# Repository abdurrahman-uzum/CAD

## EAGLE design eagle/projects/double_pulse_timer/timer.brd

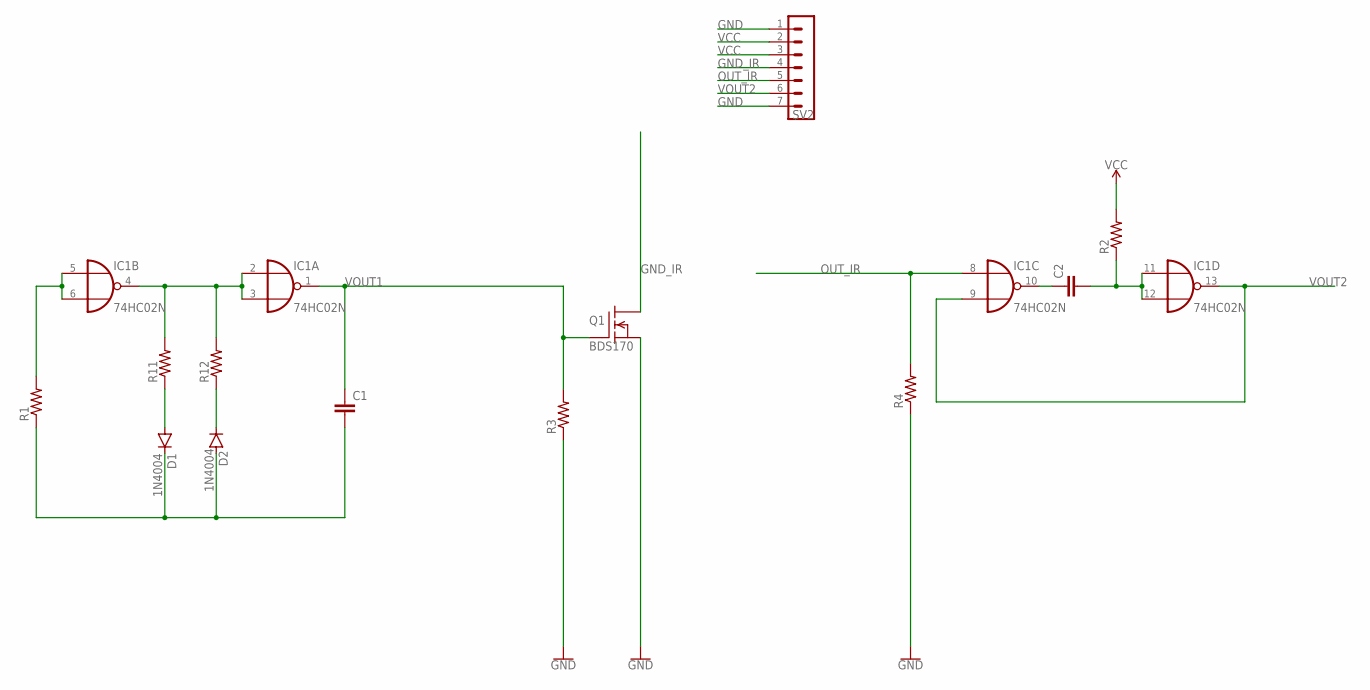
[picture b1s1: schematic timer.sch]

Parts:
C1: C-EU025-024X044; C025-024X044
C2: C-EU050-025X075; C050-025X075
D1, D2: 1N4004; DO41-10
IC1: 74HC02N; DIL14
Q1: VN10KM; TO92-
R1, R2, R3, R4, R11, R12: R-US_0207/10; 0207/10
SV2: MA07-1

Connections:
GND: IC1.7 (GND), Q1.3 (S), R3.1, R4.1, SV2.1, SV2.7
GND_IR: Q1.1 (D), SV2.4
unnamed: IC1.2 (I0), IC1.3 (I1), IC1.4 (O), R11.2, R12.2
unnamed: IC1.5 (I0), IC1.6 (I1), R1.2
unnamed: D1.A, R11.1
unnamed: D2.C, R12.1
unnamed: C1.2, D1.C, D2.A, R1.1
unnamed: C2.2, IC1.11 (I0), IC1.12 (I1), R2.1
unnamed: C2.1, IC1.10 (O)
OUT_IR: IC1.8 (I0), R4.2, SV2.5
VCC: IC1.14 (VCC), R2.2, SV2.2, SV2.3
VOUT1: C1.1, IC1.1 (O), Q1.2 (G), R3.2
VOUT2: IC1.9 (I1), IC1.13 (O), SV2.6

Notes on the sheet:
BDS170

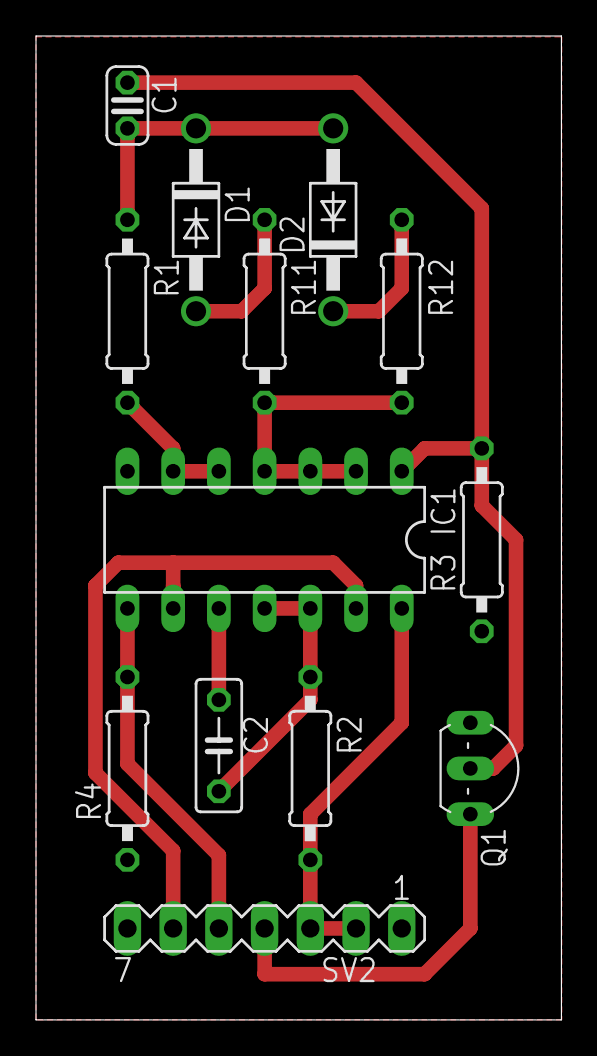
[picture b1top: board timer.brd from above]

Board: 2 copper layers, 29.2 x 54.7 mm, 13 parts (0 on the bottom side), 13 nets.

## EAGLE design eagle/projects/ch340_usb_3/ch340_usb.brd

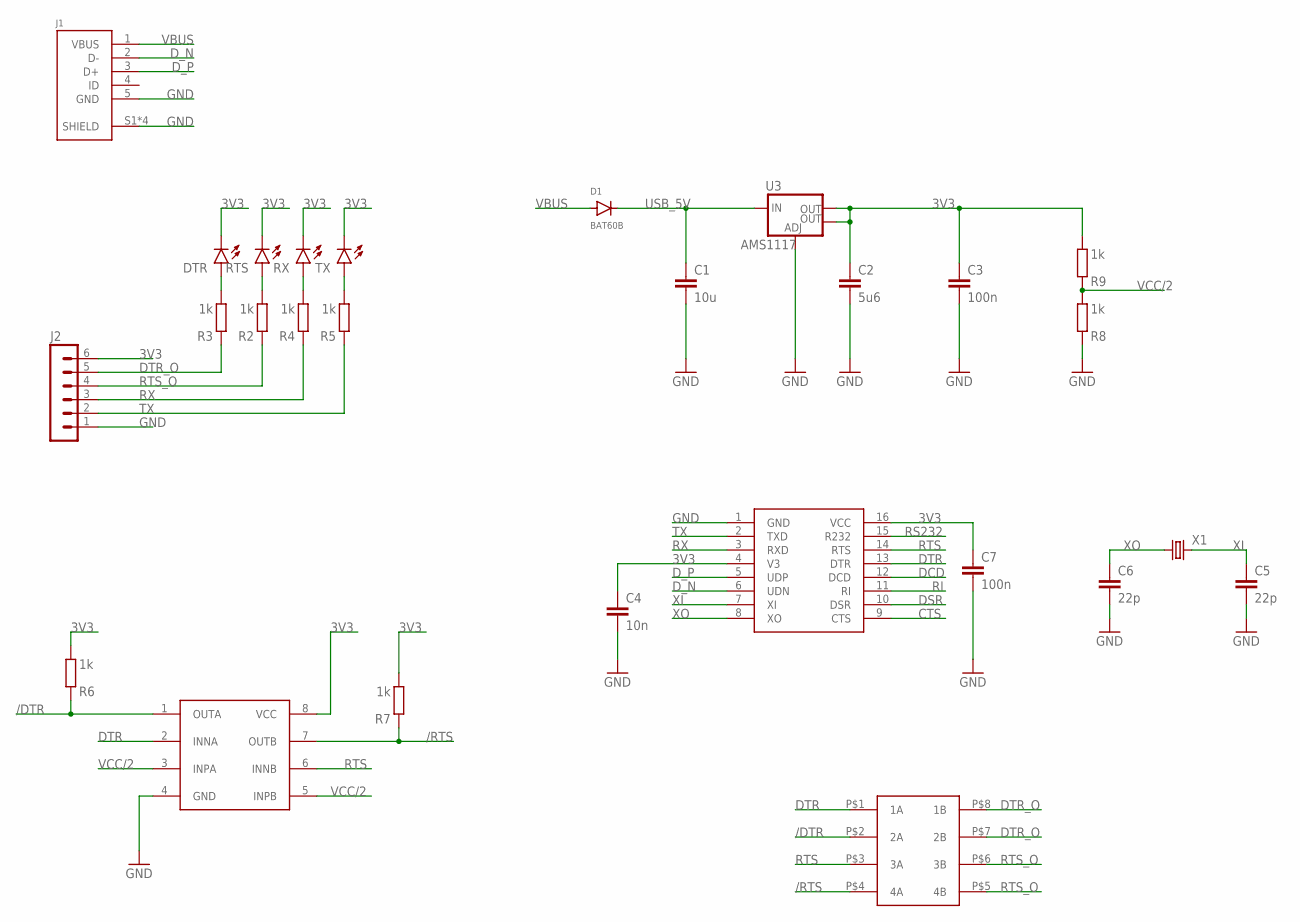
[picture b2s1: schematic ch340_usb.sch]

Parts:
C1: 10u; C0805K
C2: 5u6; C0805K
C3, C7: 100n; C0805K
C4: 10n; C0805K
C5, C6: 22p; C0805K
D1: BAT60B; SOD123
DTR: PWR; CHIPLED_0805
J1: 1734035-4
J2: MA06-1
R2, R3, R4, R5, R6, R7, R8, R9: 1k; R0805
RTS: PWR; CHIPLED_0805
RX: PWR; CHIPLED_0805
TX: PWR; CHIPLED_0805
U1: HX711; SOP16
U2: LM393; SOIC127P600X144-8
U3: AMS1117; SOT223
U$1: DIPSW4; 4_SMT_2.54
X1: CSM-7X-DU

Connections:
3V3: C2.1, C3.1, C4.1, C7.1, DTR.C, J2.6, R6.1, R7.1, R9.1, RTS.C, RX.C, TX.C, U1.4 (V3), U1.16 (VCC), U2.8 (VCC), U3.2 (OUT), U3.4 (OUT)
/DTR: R6.2, U2.1 (OUTA), U$1.P$2 (2A)
/RTS: R7.2, U2.7 (OUTB), U$1.P$4 (4A)
CTS: U1.9 (CTS)
DCD: U1.12 (DCD)
DSR: U1.10 (DSR)
DTR: U1.13 (DTR), U2.2 (INNA), U$1.P$1 (1A)
DTR_O: J2.5, R3.2, U$1.P$7 (2B), U$1.P$8 (1B)
D_N: J1.2 (D-), U1.6 (UDN)
D_P: J1.3 (D+), U1.5 (UDP)
GND: C1.2, C2.2, C3.2, C4.2, C5.2, C6.2, C7.2, J1.5 (GND), J1.S1 (SHIELD), J1.S2 (SHIELD), J1.S3 (SHIELD), J1.S4 (SHIELD), J2.1, R8.2, U1.1 (GND), U2.4 (GND), U3.1 (ADJ)
unnamed: DTR.A, R3.1
unnamed: R2.1, RTS.A
unnamed: R4.1, RX.A
unnamed: R5.1, TX.A
RI: U1.11 (RI)
RS232: U1.15 (R232)
RTS: U1.14 (RTS), U2.6 (INNB), U$1.P$3 (3A)
RTS_O: J2.4, R2.2, U$1.P$5 (4B), U$1.P$6 (3B)
RX: J2.3, R4.2, U1.3 (RXD)
TX: J2.2, R5.2, U1.2 (TXD)
USB_5V: C1.1, D1.C, U3.3 (IN)
VBUS: D1.A, J1.1 (VBUS)
VCC/2: R8.1, R9.2, U2.3 (INPA), U2.5 (INPB)
XI: C5.1, U1.7 (XI), X1.2
XO: C6.1, U1.8 (XO), X1.1

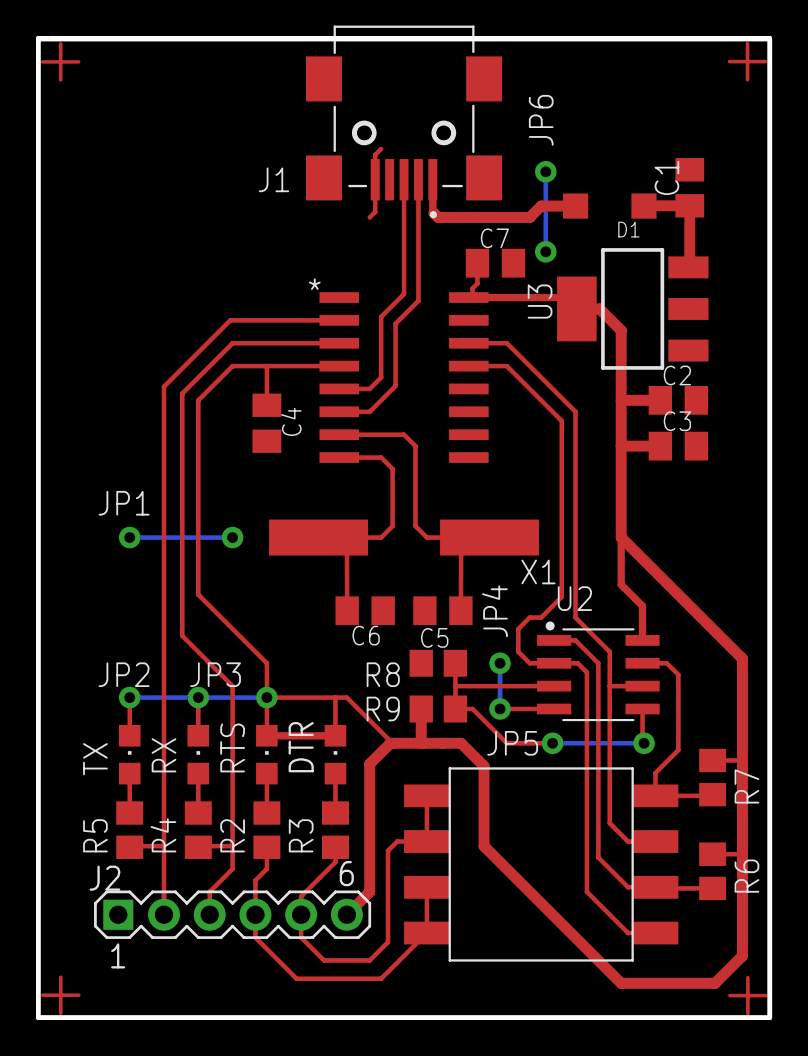
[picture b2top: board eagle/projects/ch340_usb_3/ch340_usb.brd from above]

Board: 2 copper layers, 40.6 x 54.4 mm, 27 parts (0 on the bottom side), 21 nets.

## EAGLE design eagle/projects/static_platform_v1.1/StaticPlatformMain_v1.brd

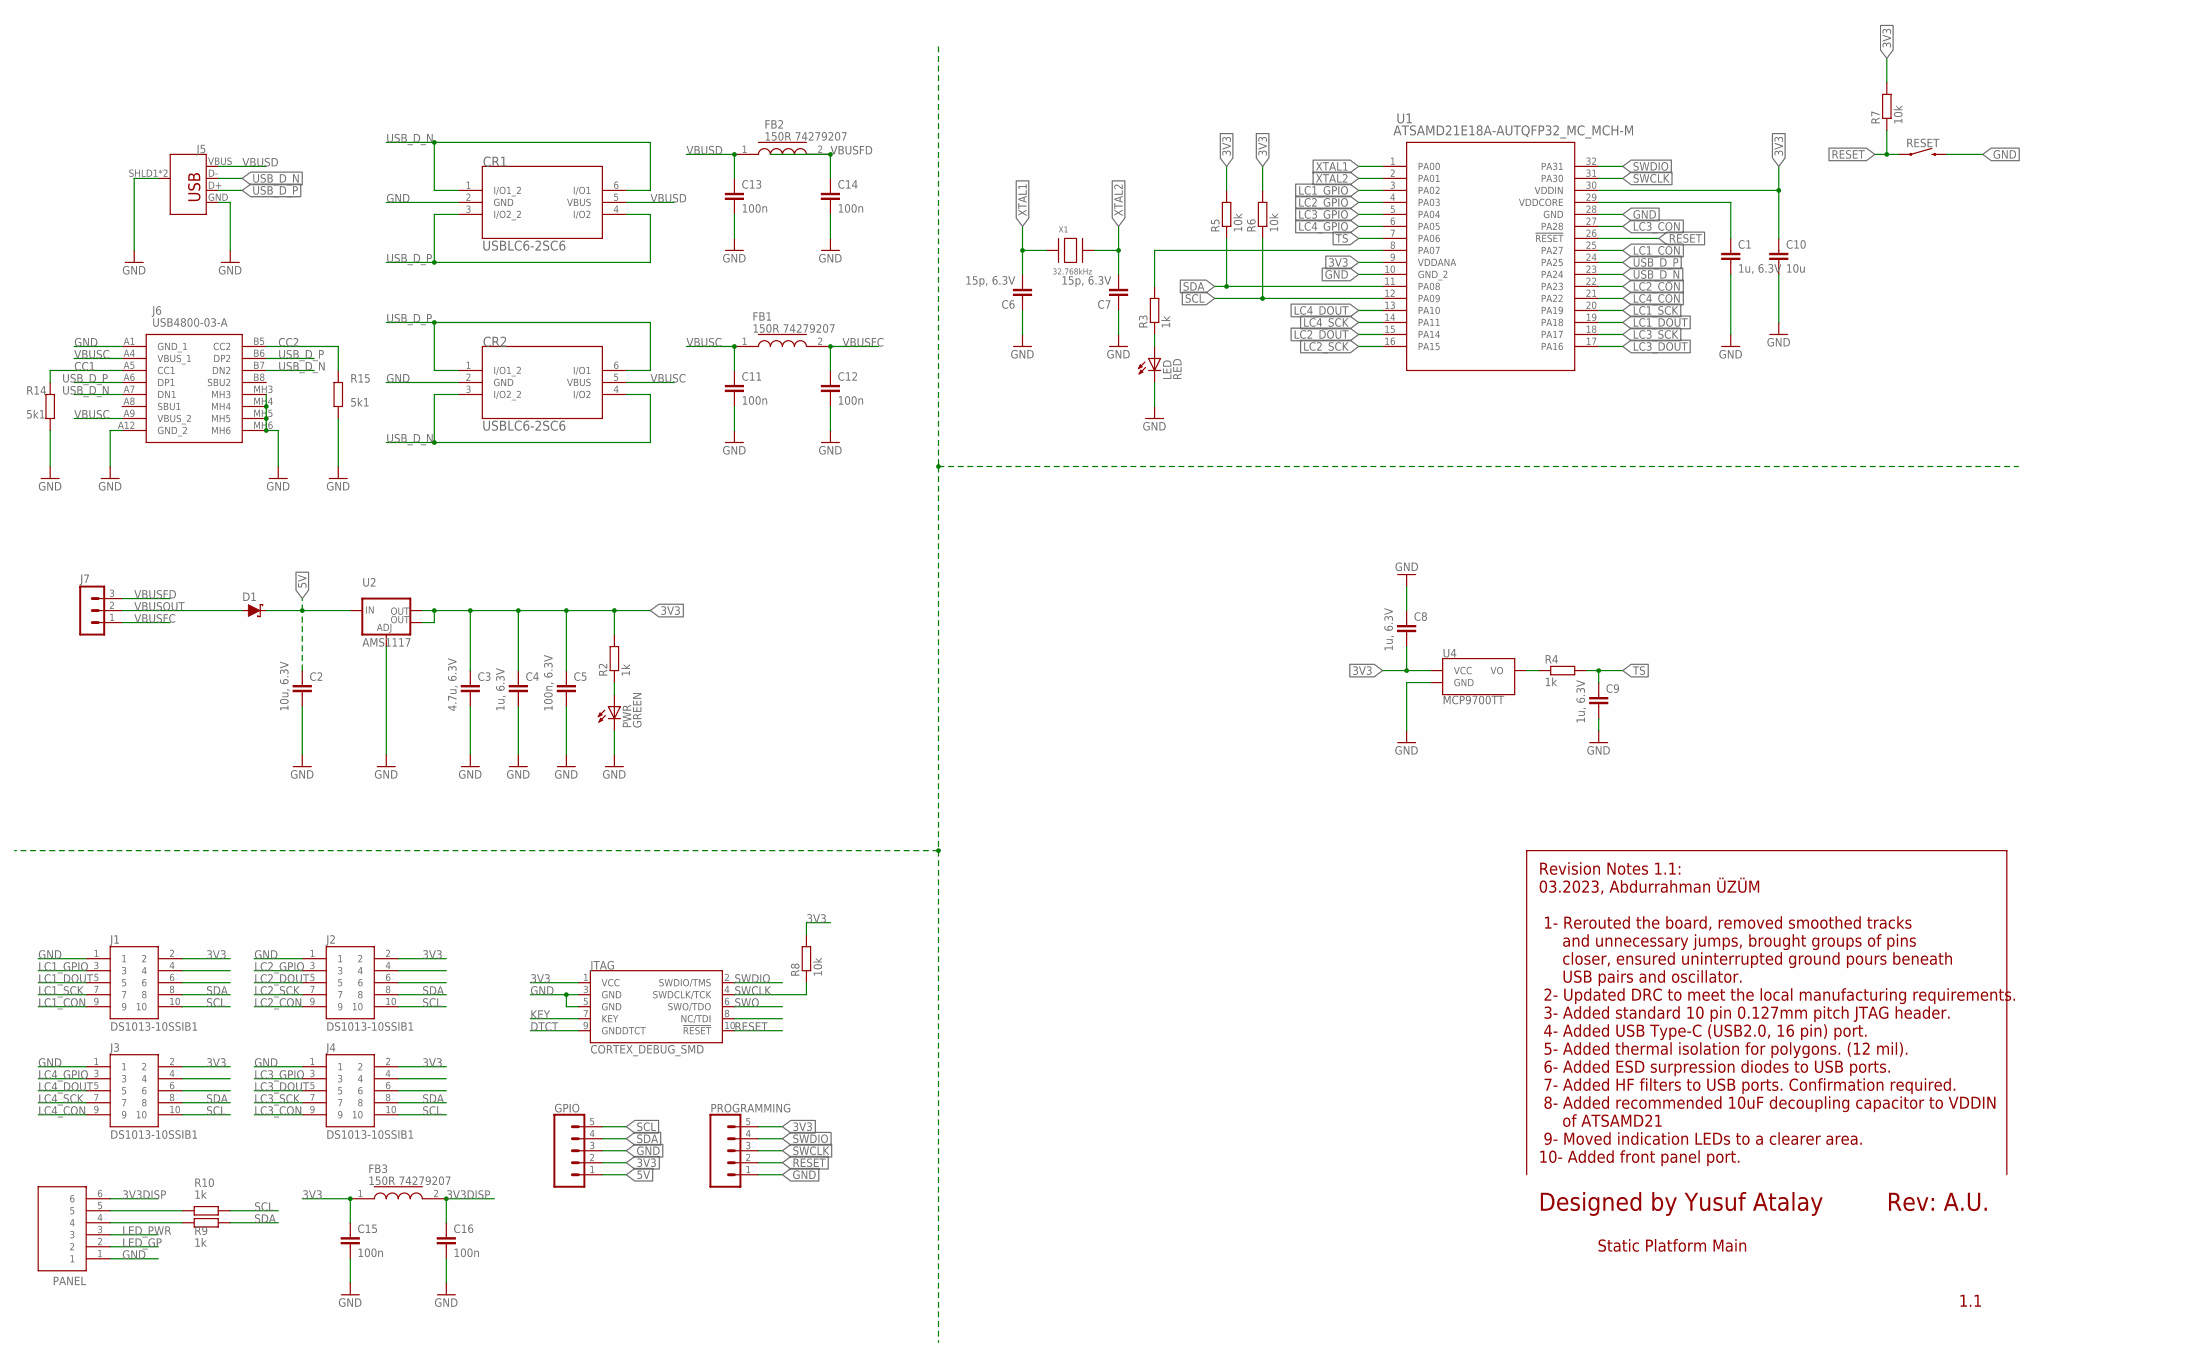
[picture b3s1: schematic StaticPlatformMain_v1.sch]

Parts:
C1, C4, C8, C9: 1u, 6.3V; C0805
C2: 10u, 6.3V; C0805
C3: 4.7u, 6.3V; C0805
C5: 100n, 6.3V; C0805
C6, C7: 15p, 6.3V; C0805
C10: 10u; C0805
C11, C12, C13, C14, C15, C16: 100n; C0805
CR1, CR2: USBLC6-2SC6; SOT23-6L_STM
D1: 3A/10V/280mV; SOD-323
FB1, FB2, FB3: 150R 74279207; CAPC2012X90N
GPIO: CONN_05NO_SILK; 1X05_NO_SILK
J1, J2, J3, J4: DS1013-10SSIB1; CONNFLY_DS1013-10SSIB1
J5: USB_B_PTH; USB-B-PTH
J6: USB4800-03-A; USB480003A
J7: MA03-1
JTAG: CORTEX_DEBUG_SMD; SAMTECH_FTSH-105-01
LED: RED; CHIPLED_0805
PANEL: S3B-XH-A(LF)(SN); JST_S3B-XH-A(LF)(SN)
PROGRAMMING: CONN_05NO_SILK; 1X05_NO_SILK
PWR: GREEN; CHIPLED_0805
R2, R3, R4, R9, R10: 1k; R0805
R5, R6, R7, R8: 10k; R0805
R14, R15: 5k1; R0805
RESET: MOMENTARY-SWITCH-SPST-SMD-6.0X3.5MM; TACTILE_SWITCH_SMD_6.0X3.5MM
U1: ATSAMD21E18A-AUTQFP32_MC_MCH-M; TQFP32_MC_MCH-M
U2: AMS1117; SOT223
U4: MCP9700TT; SOT23-3
X1: 32.768kHz; XTAL3215

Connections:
3V1: R3.2, U1.8 (PA07)
3V3: C3.1, C4.1, C5.1, C8.2, C10.1, C15.1, FB3.1, GPIO.2, J1.2, J2.2, J3.2, J4.2, JTAG.1 (VCC), PROGRAMMING.5, R2.2, R5.2, R6.2, R7.2, R8.2, U1.9 (VDDANA), U1.30 (VDDIN), U2.2 (OUT), U2.4 (OUT), U4.1 (VCC)
3V3DISP: C16.1, FB3.2, PANEL.6
5V: C2.1, D1.C, GPIO.1, U2.3 (IN)
CC1: J6.A5 (CC1), R14.2
CC2: J6.B5 (CC2), R15.2
DTCT: JTAG.9 (GNDDTCT)
GND: C1.2, C2.2, C3.2, C4.2, C5.2, C6.1, C7.1, C8.1, C9.2, C10.2, C11.2, C12.2, C13.2, C14.2, C15.2, C16.2, CR1.2 (GND), CR2.2 (GND), GPIO.3, J1.1, J2.1, J3.1, J4.1, J5.GND, J5.SHLD1 (SHIELD), J5.SHLD2 (SHIELD), J6.A1 (GND_1), J6.A12 (GND_2), J6.MH3, J6.MH4, J6.MH5, J6.MH6, JTAG.3 (GND), JTAG.5 (GND), LED.C, PANEL.1, PROGRAMMING.1, PWR.C, R14.1, R15.1, RESET.2, U1.10 (GND_2), U1.28 (GND), U2.1 (ADJ), U4.3 (GND)
KEY: JTAG.7 (KEY)
LC1_CON: J1.9, U1.25 (PA27)
LC1_DOUT: J1.5, U1.19 (PA18)
LC1_GPIO: J1.3, U1.3 (PA02)
LC1_SCK: J1.7, U1.20 (PA19)
LC2_CON: J2.9, U1.22 (PA23)
LC2_DOUT: J2.5, U1.15 (PA14)
LC2_GPIO: J2.3, U1.4 (PA03)
LC2_SCK: J2.7, U1.16 (PA15)
LC3_CON: J4.9, U1.27 (PA28)
LC3_DOUT: J4.5, U1.17 (PA16)
LC3_GPIO: J4.3, U1.5 (PA04)
LC3_SCK: J4.7, U1.18 (PA17)
LC4_CON: J3.9, U1.21 (PA22)
LC4_DOUT: J3.5, U1.13 (PA10)
LC4_GPIO: J3.3, U1.6 (PA05)
LC4_SCK: J3.7, U1.14 (PA11)
LED_GP: LED.A, PANEL.2, R3.1
LED_PWR: PANEL.3, PWR.A, R2.1
unnamed: PANEL.5, R10.2
unnamed: PANEL.4, R9.2
unnamed: C1.1, U1.29 (VDDCORE)
unnamed: R4.1, U4.2 (VO)
RESET: JTAG.10 (!RESET), PROGRAMMING.2, R7.1, RESET.1, U1.26 (!RESET)
SCL: GPIO.5, J1.10, J2.10, J3.10, J4.10, R6.1, R10.1, U1.12 (PA09)
SDA: GPIO.4, J1.8, J2.8, J3.8, J4.8, R5.1, R9.1, U1.11 (PA08)
SWCLK: JTAG.4 (SWDCLK/TCK), PROGRAMMING.3, R8.1, U1.31 (PA30)
SWDIO: JTAG.2 (SWDIO/TMS), PROGRAMMING.4, U1.32 (PA31)
SWO: JTAG.6 (SWO/TDO)
TS: C9.1, R4.2, U1.7 (PA06)
USB_D_N: CR1.1 (I/O1_2), CR1.6 (I/O1), CR2.3 (I/O2_2), CR2.4 (I/O2), J5.D-, J6.A7 (DN1), J6.B7 (DN2), U1.23 (PA24)
USB_D_P: CR1.3 (I/O2_2), CR1.4 (I/O2), CR2.1 (I/O1_2), CR2.6 (I/O1), J5.D+, J6.A6 (DP1), J6.B6 (DP2), U1.24 (PA25)
VBUSC: C11.1, CR2.5 (VBUS), FB1.1, J6.A4 (VBUS_1), J6.A9 (VBUS_2)
VBUSD: C13.1, CR1.5 (VBUS), FB2.1, J5.VBUS
VBUSFC: C12.1, FB1.2, J7.1
VBUSFD: C14.1, FB2.2, J7.3
VBUSOUT: D1.A, J7.2
XTAL1: C6.2, U1.1 (PA00), X1.P$1
XTAL2: C7.2, U1.2 (PA01), X1.P$2

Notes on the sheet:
Designed by Yusuf Atalay
Rev: A.U.
Static Platform Main
1.1
Revision Notes 1.1: 03.2023, Abdurrahman ÜZÜM 1- Rerouted the board, removed smoothed tracks and unnecessary jumps, brought groups of pins closer, ensured uninterrupted ground pours beneath USB pairs and oscillator. 2- Updated DRC to meet the local manufacturing requirements. 3- Added standard 10 p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

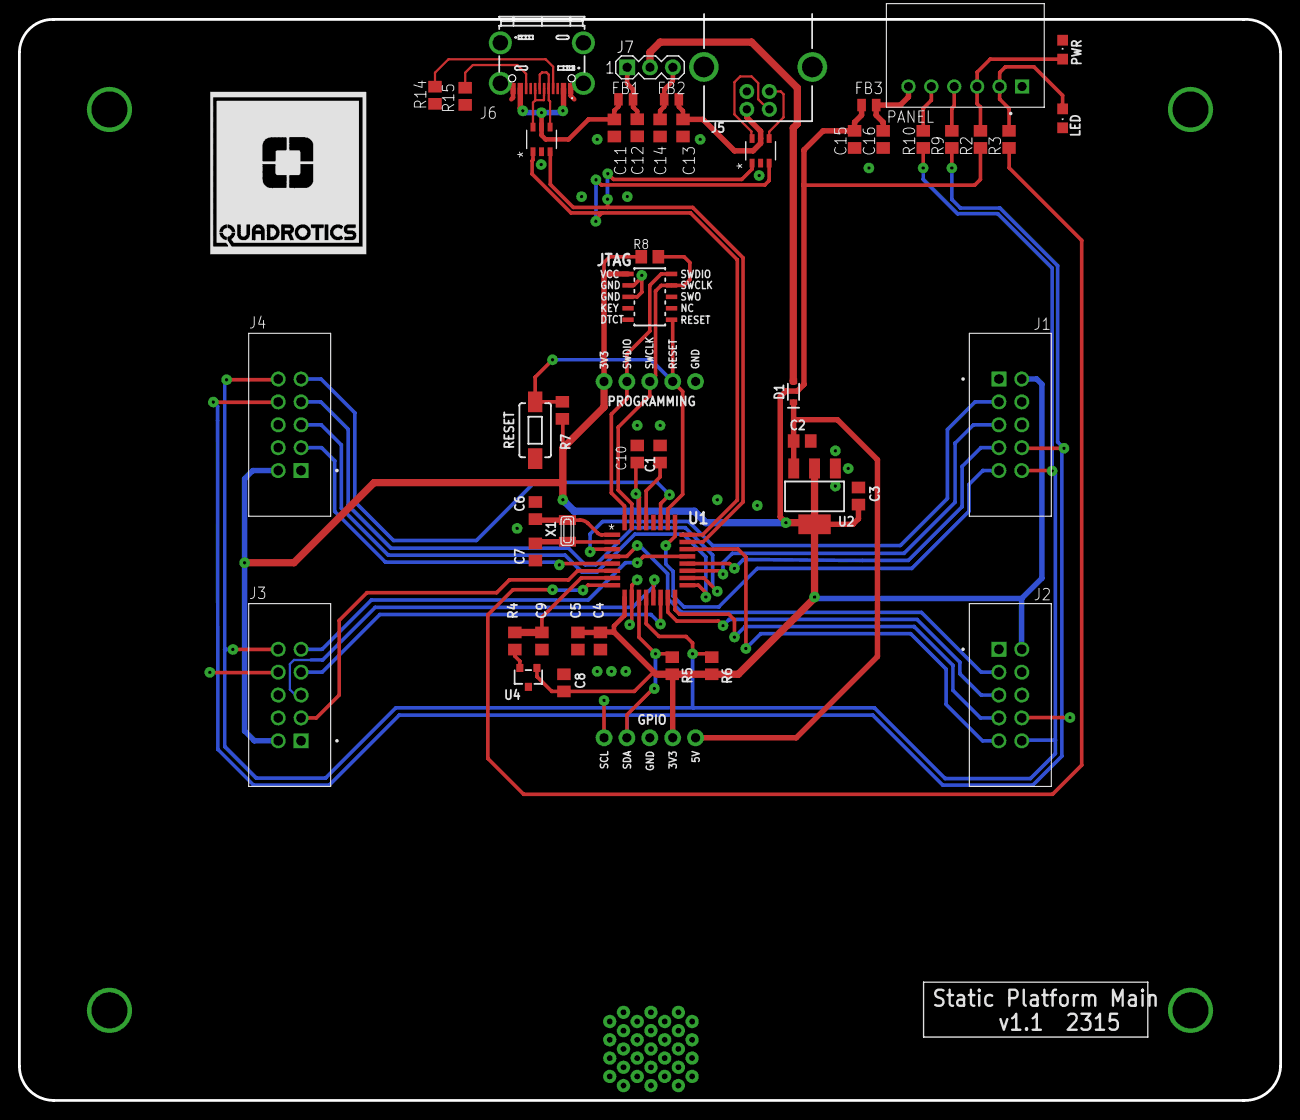
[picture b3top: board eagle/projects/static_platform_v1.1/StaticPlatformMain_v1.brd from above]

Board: 2 copper layers, 140.0 x 120.0 mm, 51 parts (0 on the bottom side), 44 nets.

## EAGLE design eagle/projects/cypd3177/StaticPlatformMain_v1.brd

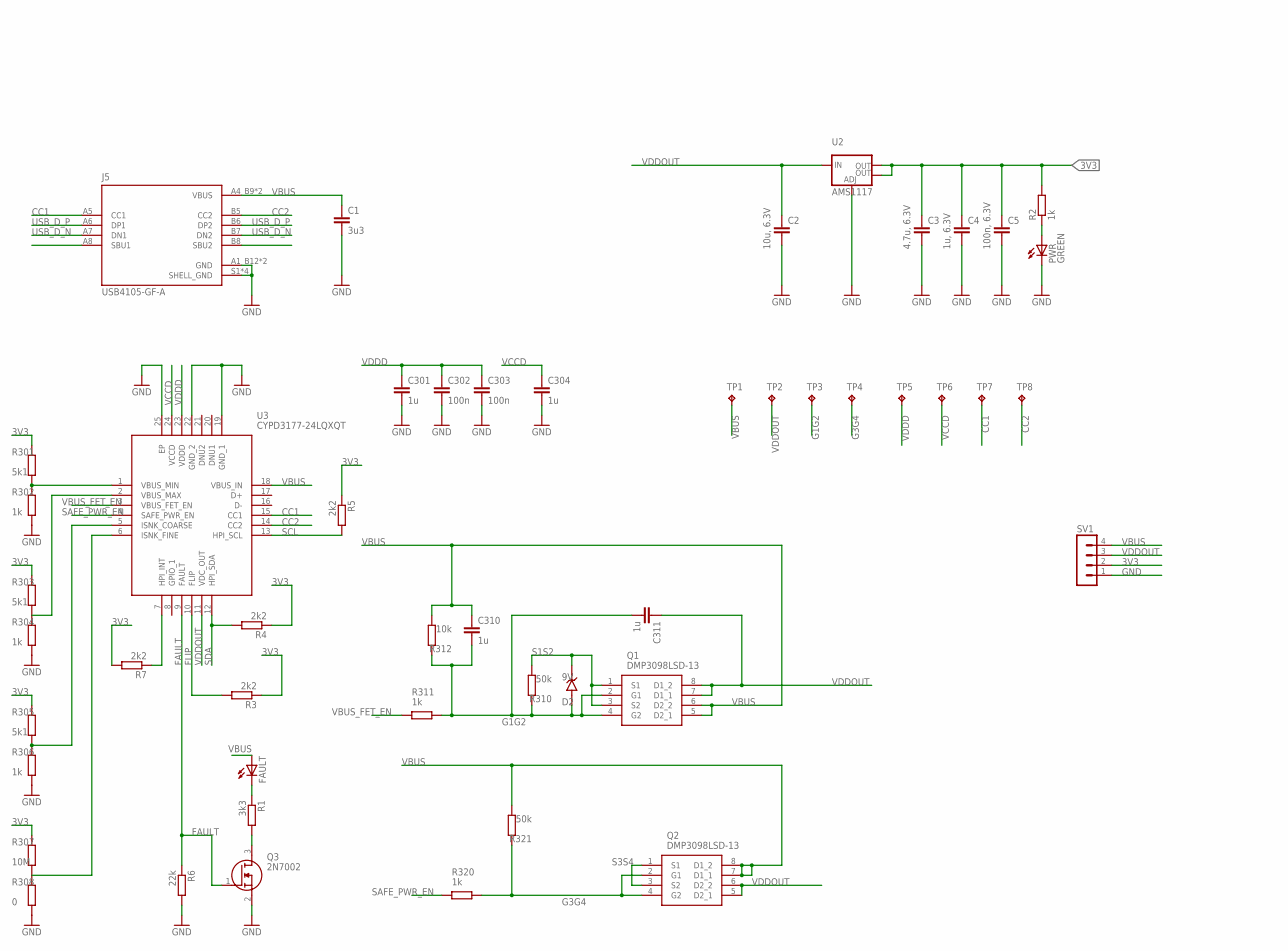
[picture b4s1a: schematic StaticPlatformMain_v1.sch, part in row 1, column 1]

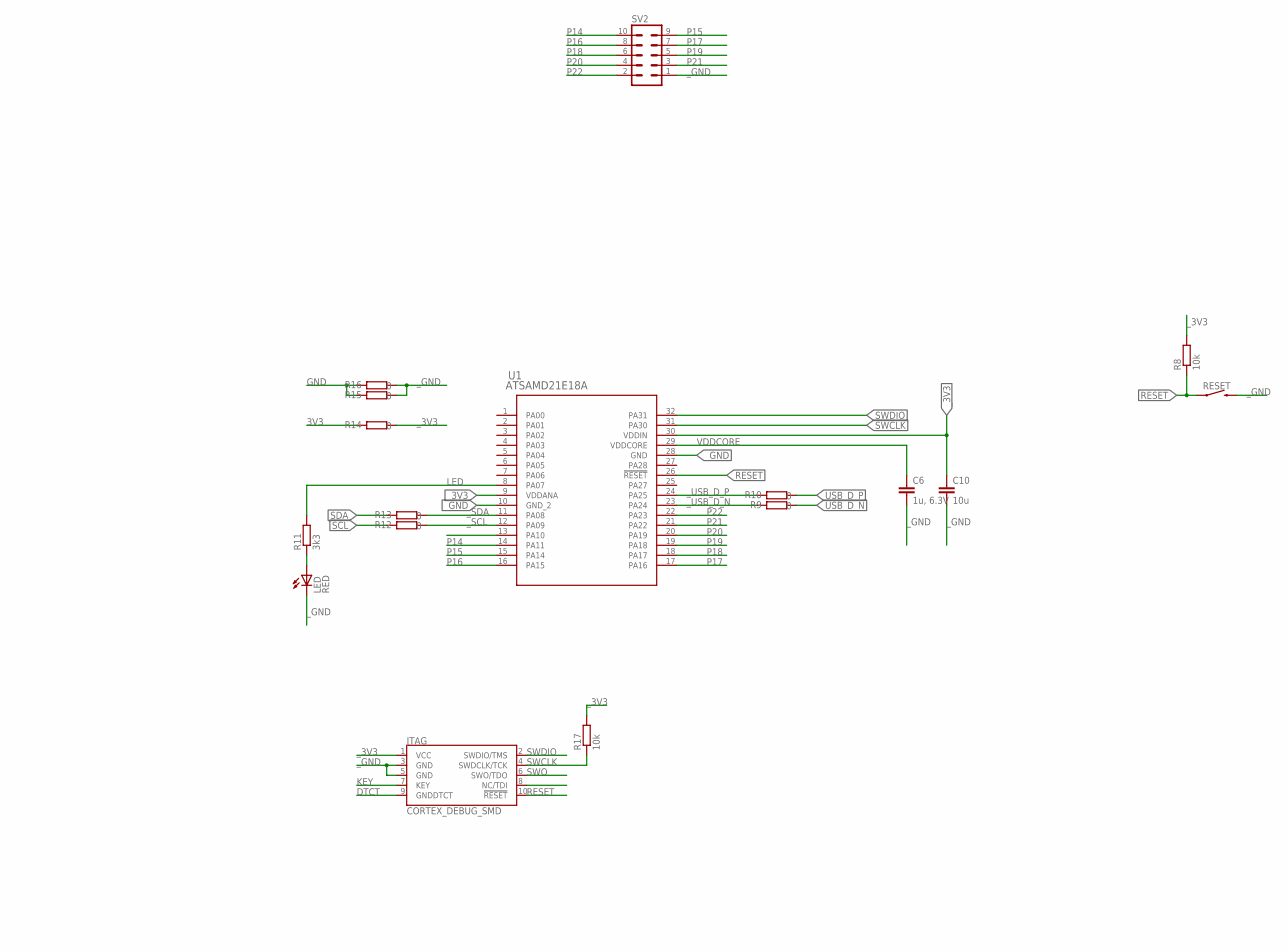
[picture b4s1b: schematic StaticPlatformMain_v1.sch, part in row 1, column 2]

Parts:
C1: 3u3; C0805K
C2: 10u, 6.3V; C0805K
C3: 4.7u, 6.3V; C0805K
C4: 1u, 6.3V; C0805K
C5: 100n, 6.3V; C0805K
C6: 1u, 6.3V; C0805
C10: 10u; C0805
C301, C304, C310, C311: 1u; C0805K
C302, C303: 100n; C0805K
D2: 9V; DIOMELF3515N
FAULT: GREEN; CHIPLED_0805
J5: USB4105-GF-A; GCT_USB4105-GF-A
JTAG: CORTEX_DEBUG_SMD; SAMTECH_FTSH-105-01
LED: RED; CHIPLED_0805
PWR: GREEN; CHIPLED_0805
Q1, Q2: DMP3098LSD-13; SOIC127P600X175-8N
Q3: 2N7002; SOT96P240X120-3N
R1, R11: 3k3; R0805
R2, R302, R304, R306, R311, R320: 1k; R0805
R3, R4, R5, R7: 2k2; R0805
R6: 22k; R0805
R8, R17, R312: 10k; R0805
R9, R10, R12, R13, R14, R15, R16, R308: 0; R0805
R301, R303, R305: 5k1; R0805
R307: 10M; R0805
R310, R321: 50k; R0805
RESET: MOMENTARY-SWITCH-SPST-SMD-6.0X3.5MM; TACTILE_SWITCH_SMD_6.0X3.5MM
SV1: MA04-1
SV2: MA05-2
TP1, TP2, TP3, TP4, TP5, TP6, TP7, TP8: TPTP18R; TP18R
U1: ATSAMD21E18A; TQFP32_MC_MCH-M
U2: AMS1117; SOT223
U3: CYPD3177-24LQXQT; QFN50P400X400X60-25N

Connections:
3V3: C3.1, C4.1, C5.1, R2.2, R3.1, R4.1, R5.1, R7.2, R14.2, R301.2, R303.2, R305.2, R307.2, SV1.2, U2.2 (OUT), U2.4 (OUT)
CC1: J5.A5 (CC1), TP7.TP, U3.15 (CC1)
CC2: J5.B5 (CC2), TP8.TP, U3.14 (CC2)
DTCT: JTAG.9 (GNDDTCT)
FAULT: Q3.1 (G), R6.1, U3.9 (FAULT)
FLIP: R3.2, U3.10 (FLIP)
G1G2: C310.2, C311.2, D2.A, Q1.2 (G1), Q1.4 (G2), R310.2, R311.1, R312.2, TP3.TP
G3G4: Q2.2 (G1), Q2.4 (G2), R320.1, R321.2, TP4.TP
GND: C1.2, C2.2, C3.2, C4.2, C5.2, C301.2, C302.2, C303.2, C304.2, J5.A1_B12 (GND), J5.B1_A12 (GND), J5.S1 (SHELL_GND), J5.S2 (SHELL_GND), J5.S3 (SHELL_GND), J5.S4 (SHELL_GND), PWR.C, Q3.2 (S), R6.2, R15.2, R16.2, R302.1, R304.1, R306.1, R308.1, SV1.1, U2.1 (ADJ), U3.19 (GND_1), U3.22 (GND_2), U3.25 (EP)
KEY: JTAG.7 (KEY)
LED: R11.2, U1.8 (PA07)
LED_GP: LED.A, R11.1
LED_PWR: PWR.A, R2.1
unnamed: FAULT.C, R1.1
unnamed: R7.1, U3.7 (HPI_INT)
unnamed: R301.1, R302.2, U3.1 (VBUS_MIN)
unnamed: R303.1, R304.2, U3.2 (VBUS_MAX)
unnamed: R305.1, R306.2, U3.5 (ISNK_COARSE)
unnamed: Q3.3 (D), R1.2
unnamed: R307.1, R308.2, U3.6 (ISNK_FINE)
P14: SV2.10, U1.14 (PA11)
P15: SV2.9, U1.15 (PA14)
P16: SV2.8, U1.16 (PA15)
P17: SV2.7, U1.17 (PA16)
P18: SV2.6, U1.18 (PA17)
P19: SV2.5, U1.19 (PA18)
P20: SV2.4, U1.20 (PA19)
P21: SV2.3, U1.21 (PA22)
P22: SV2.2, U1.22 (PA23)
RESET: JTAG.10 (!RESET), R8.1, RESET.1, U1.26 (!RESET)
S1S2: D2.C (K), Q1.1 (S1), Q1.3 (S2), R310.1
S3S4: Q2.1 (S1), Q2.3 (S2)
SAFE_PWR_EN: R320.2, U3.4 (SAFE_PWR_EN)
SCL: R5.2, R12.2, U3.13 (HPI_SCL)
SDA: R4.2, R13.2, U3.12 (HPI_SDA)
SWCLK: JTAG.4 (SWDCLK/TCK), R17.1, U1.31 (PA30)
SWDIO: JTAG.2 (SWDIO/TMS), U1.32 (PA31)
SWO: JTAG.6 (SWO/TDO)
USB_D_N: J5.A7 (DN1), J5.B7 (DN2), R9.1
USB_D_P: J5.A6 (DP1), J5.B6 (DP2), R10.1
VBUS: C1.1, C310.1, FAULT.A, J5.A4_B9 (VBUS), J5.B4_A9 (VBUS), Q1.5 (D2_1), Q1.6 (D2_2), Q2.7 (D1_1), Q2.8 (D1_2), R312.1, R321.1, SV1.4, TP1.TP, U3.18 (VBUS_IN)
VBUS_FET_EN: R311.2, U3.3 (VBUS_FET_EN)
VCCD: C304.1, TP6.TP, U3.24 (VCCD)
VDDCORE: C6.1, U1.29 (VDDCORE)
VDDD: C301.1, C302.1, C303.1, TP5.TP, U3.23 (VDDD)
VDDOUT: C2.1, C311.1, Q1.7 (D1_1), Q1.8 (D1_2), Q2.5 (D2_1), Q2.6 (D2_2), SV1.3, TP2.TP, U2.3 (IN), U3.11 (VDC_OUT)
_3V3: C10.1, JTAG.1 (VCC), R8.2, R14.1, R17.2, U1.9 (VDDANA), U1.30 (VDDIN)
_GND: C6.2, C10.2, JTAG.3 (GND), JTAG.5 (GND), LED.C, R15.1, R16.1, RESET.2, SV2.1, U1.10 (GND_2), U1.28 (GND)
_SCL: R12.1, U1.12 (PA09)
_SDA: R13.1, U1.11 (PA08)
_USB_D_N: R9.2, U1.23 (PA24)
_USB_D_P: R10.2, U1.24 (PA25)

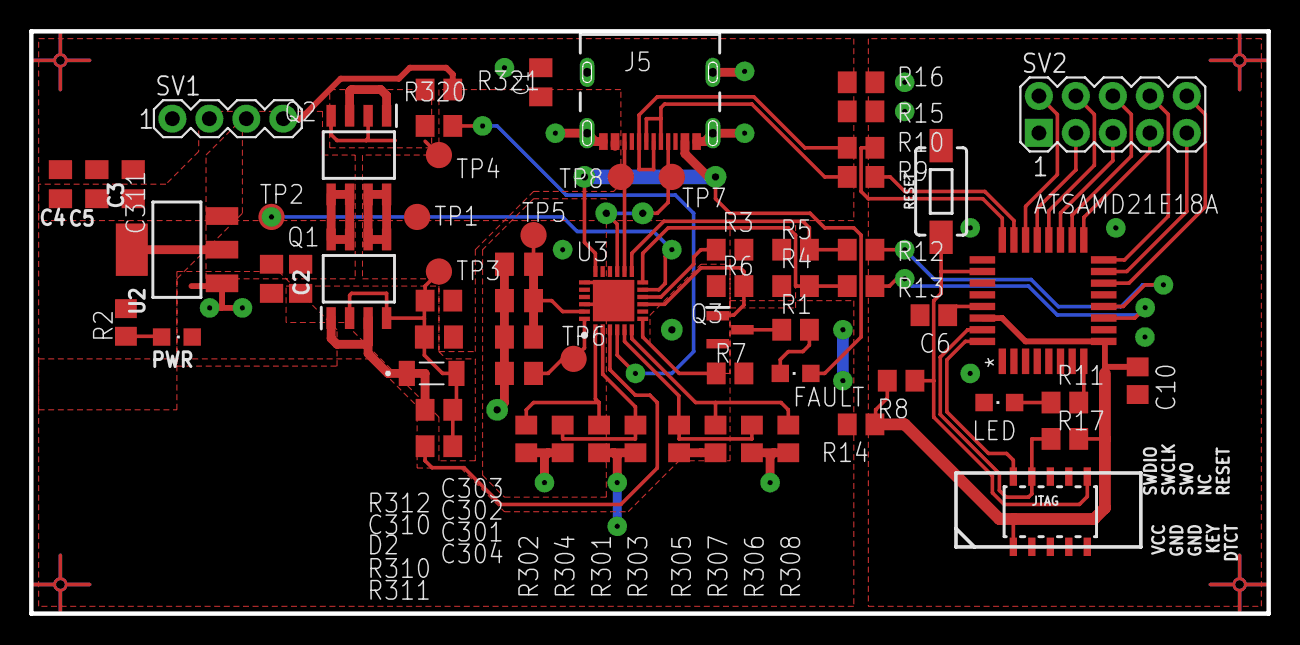
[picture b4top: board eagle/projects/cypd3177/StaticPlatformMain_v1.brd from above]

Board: 2 copper layers, 85.0 x 40.0 mm, 66 parts (0 on the bottom side), 49 nets.

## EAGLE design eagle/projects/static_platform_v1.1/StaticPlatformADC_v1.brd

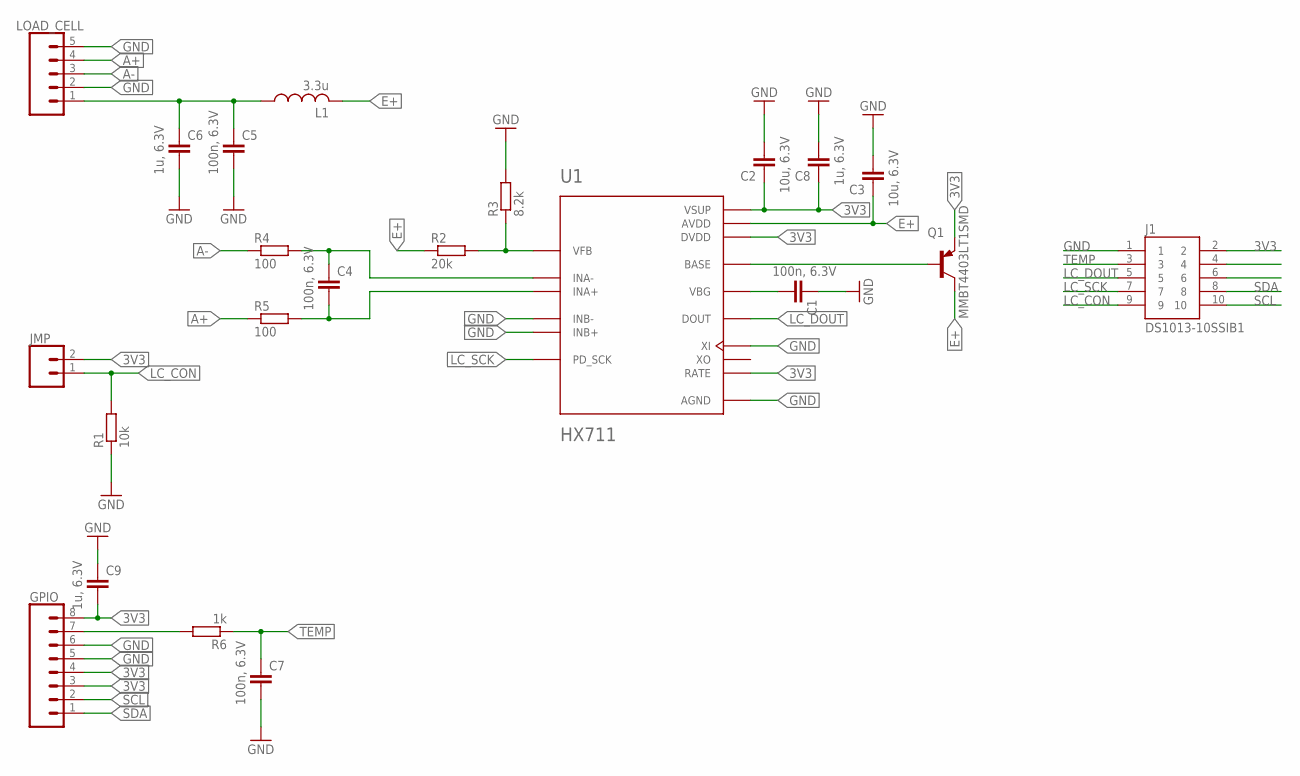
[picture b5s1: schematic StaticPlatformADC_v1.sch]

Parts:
C1, C4, C5, C7: 100n, 6.3V; C0805
C2, C3: 10u, 6.3V; C0805
C6, C8, C9: 1u, 6.3V; C0805
GPIO: CONN_08NO_SILK_FEMALE_PTH; 1X08_NO_SILK
J1: DS1013-10SSIB1; CONNFLY_DS1013-10SSIB1
JMP: CONN_021X02_NO_SILK; 1X02_NO_SILK
L1: 3.3u; L3225P
LOAD_CELL: CONN_05NO_SILK; 1X05_NO_SILK
Q1: MMBT4403LT1SMD; SOT23-BEC
R1: 10k; R0805
R2: 20k; R0805
R3: 8.2k; R0805
R4, R5: 100; R0805
R6: 1k; R0805
U1: HX711; SOP127P600X180-16N

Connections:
3V3: C2.1, C8.1, C9.2, GPIO.3, GPIO.4, GPIO.8, J1.2, JMP.2, Q1.E, U1.1 (VSUP), U1.15 (RATE), U1.16 (DVDD)
A+: LOAD_CELL.4, R5.1
A-: LOAD_CELL.3, R4.1
E+: C3.1, L1.2, Q1.C, R2.1, U1.3 (AVDD)
GND: C1.1, C2.2, C3.2, C5.2, C6.2, C7.2, C8.2, C9.1, GPIO.5, GPIO.6, J1.1, LOAD_CELL.2, LOAD_CELL.5, R1.1, R3.2, U1.5 (AGND), U1.9 (INB-), U1.10 (INB+), U1.14 (XI)
LC_CON: J1.9, JMP.1, R1.2
LC_DOUT: J1.5, U1.12 (DOUT)
LC_SCK: J1.7, U1.11 (PD_SCK)
unnamed: C5.1, C6.1, L1.1, LOAD_CELL.1
unnamed: Q1.B, U1.2 (BASE)
unnamed: R2.2, R3.1, U1.4 (VFB)
unnamed: C1.2, U1.6 (VBG)
unnamed: GPIO.7, R6.2
unnamed: C4.1, R4.2, U1.7 (INA-)
unnamed: C4.2, R5.2, U1.8 (INA+)
SCL: GPIO.2, J1.10
SDA: GPIO.1, J1.8
TEMP: C7.1, J1.3, R6.1

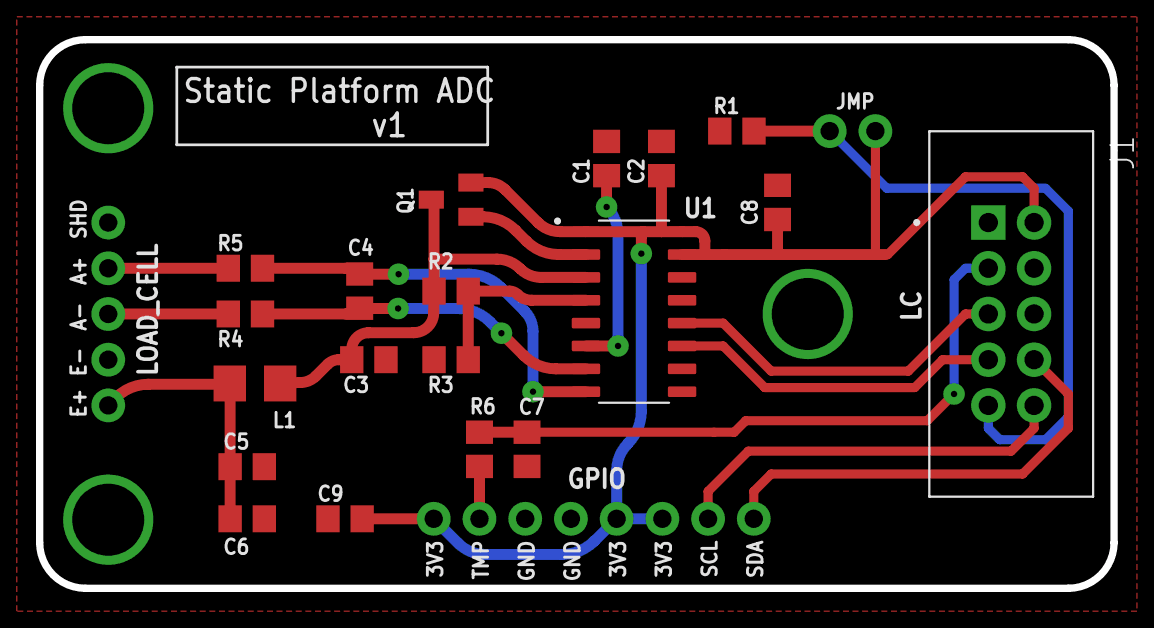
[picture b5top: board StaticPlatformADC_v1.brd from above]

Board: 2 copper layers, 59.7 x 30.5 mm, 22 parts (0 on the bottom side), 18 nets.

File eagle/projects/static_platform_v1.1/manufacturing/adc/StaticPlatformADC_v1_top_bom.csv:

Comment,Designator,Footprint,LCSC Part #
1k,R6,R0805,
1u  6.3V,C6,C0805,
1u  6.3V,C8,C0805,
1u  6.3V,C9,C0805,
3.3u,L1,L3225P,
8.2k,R3,R0805,
10k,R1,R0805,
10u  6.3V,C2,C0805,
10u  6.3V,C3,C0805,
20k,R2,R0805,
100,R4 R5,R0805,
100n  6.3V,C1,C0805,
100n  6.3V,C4,C0805,
100n  6.3V,C5,C0805,
100n  6.3V,C7,C0805,
HX711,U1,SOP127P600X180-16N,
MMBT4403LT1SMD,Q1,SOT23-BEC,

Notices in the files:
parts and their libraries:
SparkFun-IC-Power: Licensing: Creative Commons ShareAlike 4.0 International - https://creativecommons.org/licenses/by-sa/4.0
COPYRIGHT: Copyright (C) 2022 Ultra Librarian. All rights reserved.
COPYRIGHT: Copyright (C) 2023 Ultra Librarian. All rights reserved.
